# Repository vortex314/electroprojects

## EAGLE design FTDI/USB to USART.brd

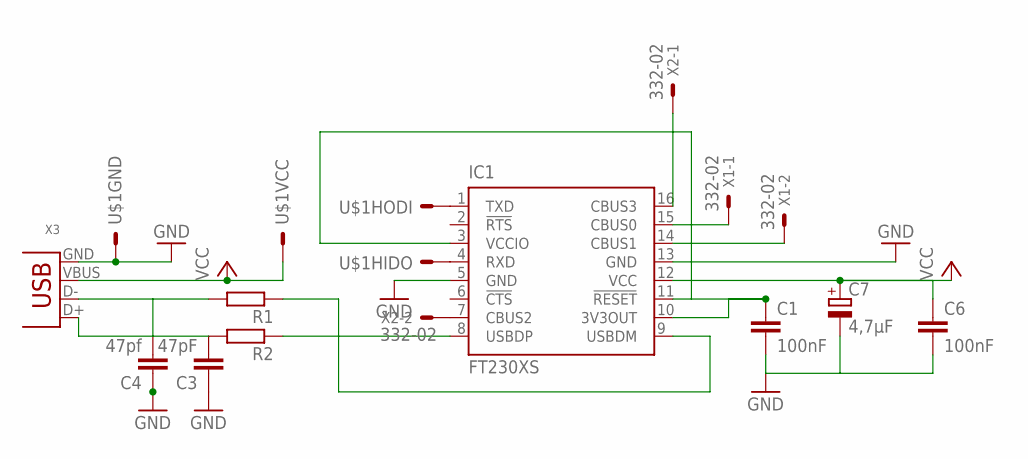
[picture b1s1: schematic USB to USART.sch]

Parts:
C1, C6: 100nF; C025-030X050
C3: 47pF; C025-030X050
C4: 47pf; C025-030X050
C7: 4,7µF; B45181B
IC1: FT230XS; SSOP16
R1, R2: R-EU_0204/7; 0204/7
U$1: UARTUSB; PN61729
X1, X2: 332-02
X3: USB-B-H

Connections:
GND: C1.2, C3.1, C4.1, C6.2, C7.-, IC1.5 (GND), IC1.13 (GND), U$1.4, X3.GND
unnamed: IC1.8 (USBDP), R2.1
unnamed: C3.2, R2.2, X3.D+
unnamed: IC1.9 (USBDM), R1.1
unnamed: C1.1, IC1.3 (VCCIO), IC1.10 (3V3OUT), IC1.11 (!RESET)
unnamed: C4.2, R1.2, X3.D-
unnamed: IC1.1 (TXD), U$1.3
unnamed: IC1.4 (RXD), U$1.2
unnamed: IC1.14 (CBUS1), X1.2
unnamed: IC1.15 (CBUS0), X1.1
unnamed: IC1.16 (CBUS3), X2.1
unnamed: IC1.7 (CBUS2), X2.2
VCC: C6.1, C7.+, IC1.12 (VCC), U$1.1, X3.VBUS

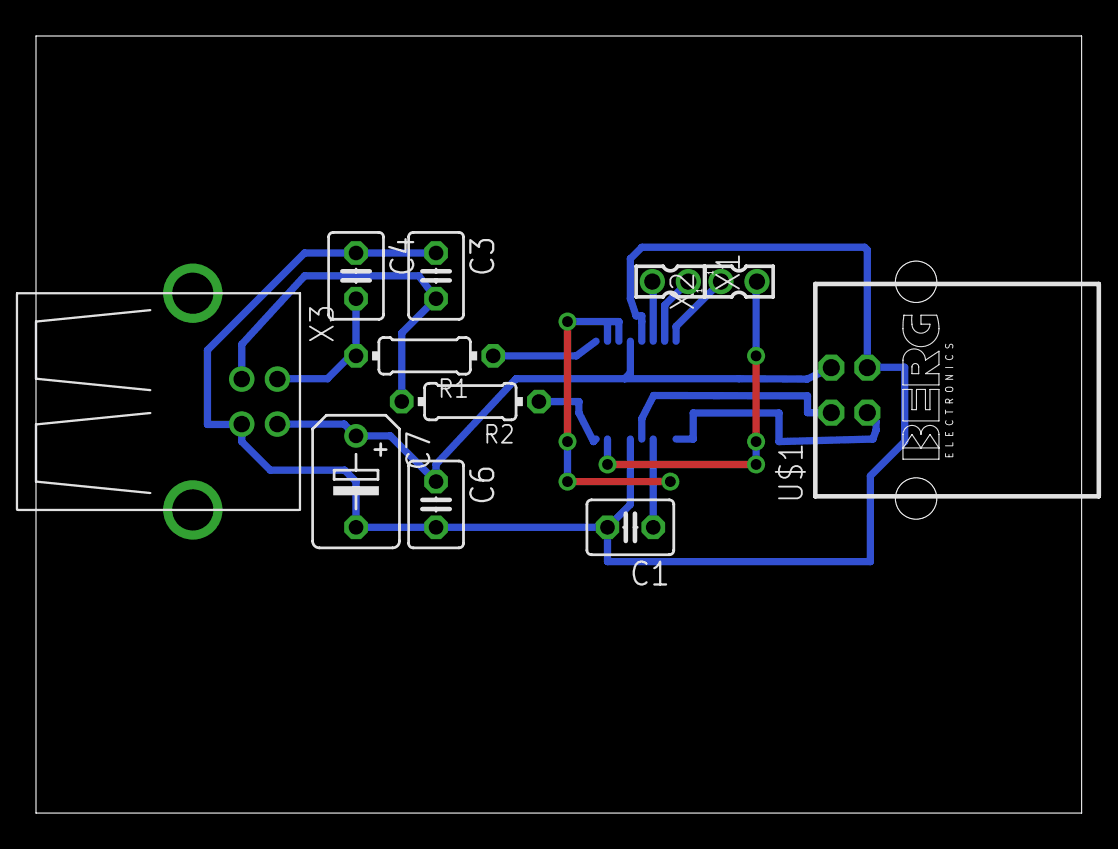
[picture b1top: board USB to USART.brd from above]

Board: 2 copper layers, 58.1 x 43.2 mm, 12 parts (1 on the bottom side), 13 nets.

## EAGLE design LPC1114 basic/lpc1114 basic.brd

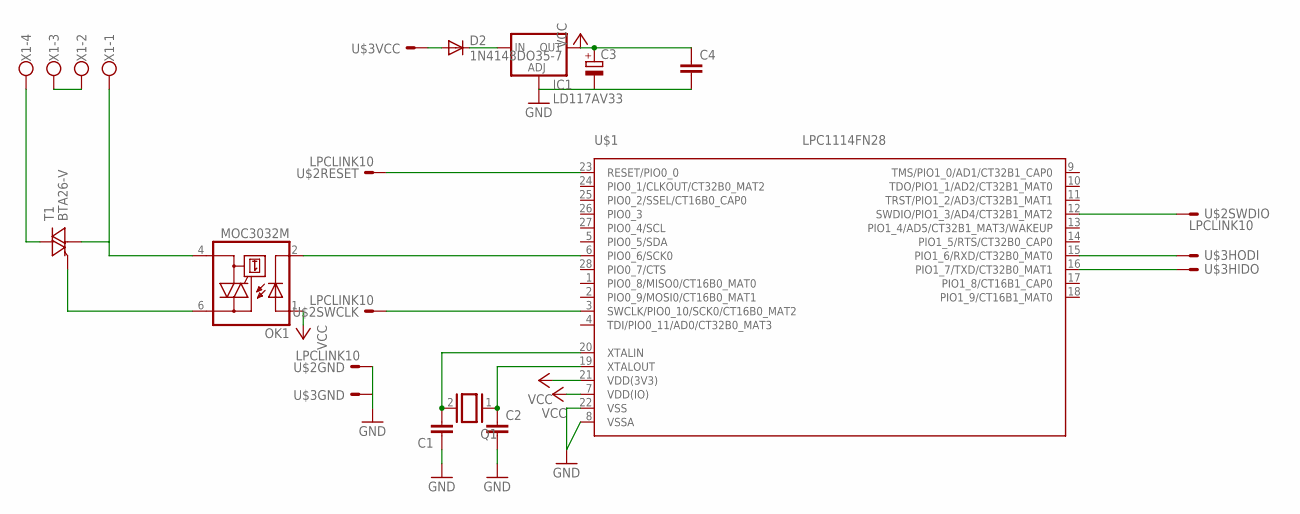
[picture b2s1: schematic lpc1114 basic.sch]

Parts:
C1, C2: C-EU025-024X044; C025-024X044
C3: CPOL-EUTT2D6; TT2D6
C4: C-EU050-024X044; C050-024X044
D2: 1N4148DO35-7; DO35-7
IC1: LD117AV33; TO220L1
OK1: MOC3032M; DIL06
Q1: XTAL/S; QS
T1: BTA26-V; TOP3S-1
U$1: LPC1114FN28; DIP28
U$2: LPCLINK10; ML10
U$3: UARTUSB; PN61729
X1: W237-4

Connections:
GND: C1.1, C2.2, C3.-, C4.2, IC1.1 (ADJ), U$1.8 (VSSA), U$1.22 (VSS), U$2.9, U$3.4
unnamed: C1.2, Q1.2, U$1.20 (XTALIN)
unnamed: C2.1, Q1.1, U$1.19 (XTALOUT)
unnamed: U$1.15 (PIO1_6/RXD/CT32B0_MAT0), U$3.3
unnamed: U$1.16 (PIO1_7/TXD/CT32B0_MAT1), U$3.2
unnamed: U$1.3 (SWCLK/PIO0_10/SCK0/CT16B0_MAT2), U$2.4
unnamed: U$1.12 (SWDIO/PIO1_3/AD4/CT32B1_MAT2), U$2.2
unnamed: U$1.23 (RESET/PIO0_0), U$2.10
unnamed: D2.A, U$3.1
unnamed: OK1.6 (A2), T1.G
unnamed: D2.C, IC1.3 (IN)
unnamed: T1.A2, X1.4
unnamed: OK1.2 (C), U$1.6 (PIO0_6/SCK0)
unnamed: OK1.4 (A1), T1.A1, X1.1
unnamed: X1.2, X1.3
VCC: C3.+, C4.1, IC1.2 (OUT), OK1.1 (A), U$1.7 (VDD(IO)), U$1.21 (VDD(3V3))

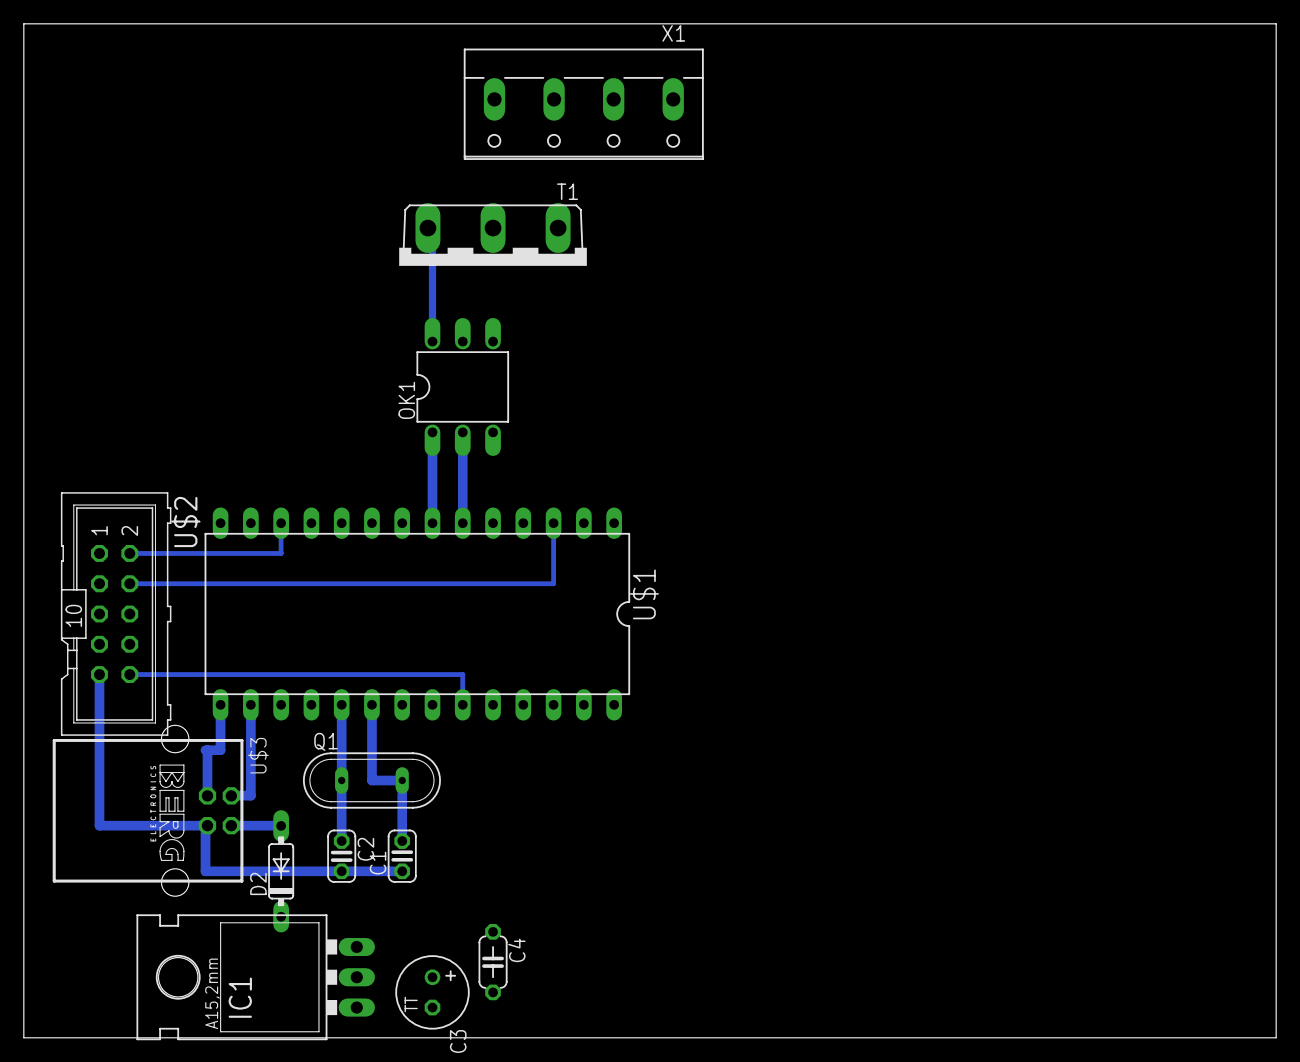
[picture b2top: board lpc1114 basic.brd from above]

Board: 2 copper layers, 105.1 x 85.1 mm, 13 parts (0 on the bottom side), 16 nets.

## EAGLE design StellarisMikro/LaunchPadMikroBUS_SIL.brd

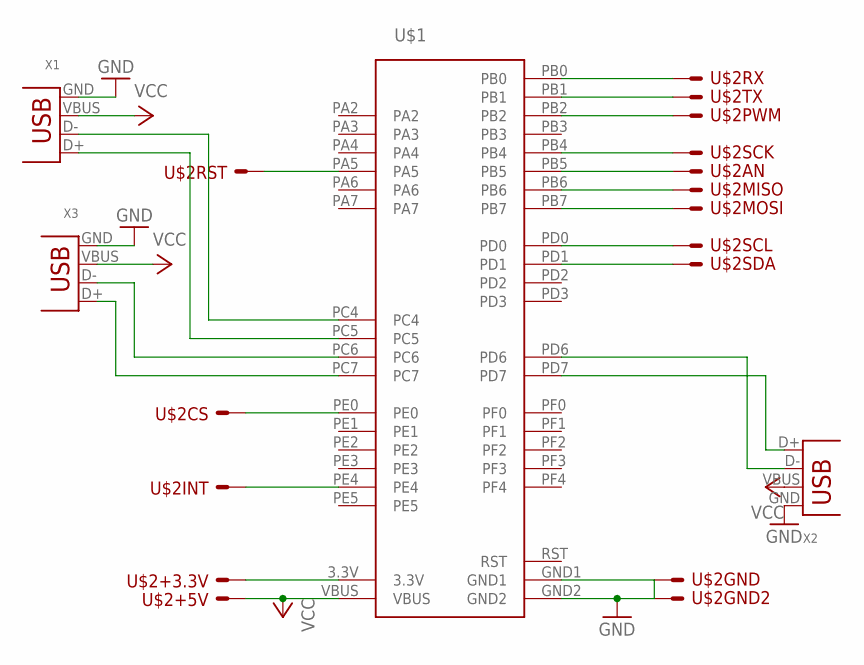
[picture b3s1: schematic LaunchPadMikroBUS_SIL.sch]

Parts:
U$1: STELLARIS-LAUNCHPADSTELLARIS-LAUNCHPAD-XL; LAUNCHPAD-XL
U$2: MIKROBUSSIL; MIKROBUS_SIL
X1, X2, X3: USB-A-H

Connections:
GND: U$1.GND1, U$1.GND2, U$2.GND, U$2.GND2, X1.GND, X2.GND, X3.GND
unnamed: U$1.PB2, U$2.PWM
unnamed: U$1.PE4, U$2.INT
unnamed: U$1.PB0, U$2.RX
unnamed: U$1.PB1, U$2.TX
unnamed: U$1.PD0, U$2.SCL
unnamed: U$1.PD1, U$2.SDA
unnamed: U$1.PC7, X3.D+
unnamed: U$1.PC6, X3.D-
unnamed: U$1.PC5, X1.D+
unnamed: U$1.3.3V, U$2.+3.3V
unnamed: U$1.PB5, U$2.AN
unnamed: U$1.PA5, U$2.RST
unnamed: U$1.PE0, U$2.CS
unnamed: U$1.PB4, U$2.SCK
unnamed: U$1.PB7, U$2.MOSI
unnamed: U$1.PB6, U$2.MISO
unnamed: U$1.PC4, X1.D-
unnamed: U$1.PD7, X2.D+
unnamed: U$1.PD6, X2.D-
RST: U$1.RST
VCC: U$1.VBUS, U$2.+5V, X1.VBUS, X2.VBUS, X3.VBUS

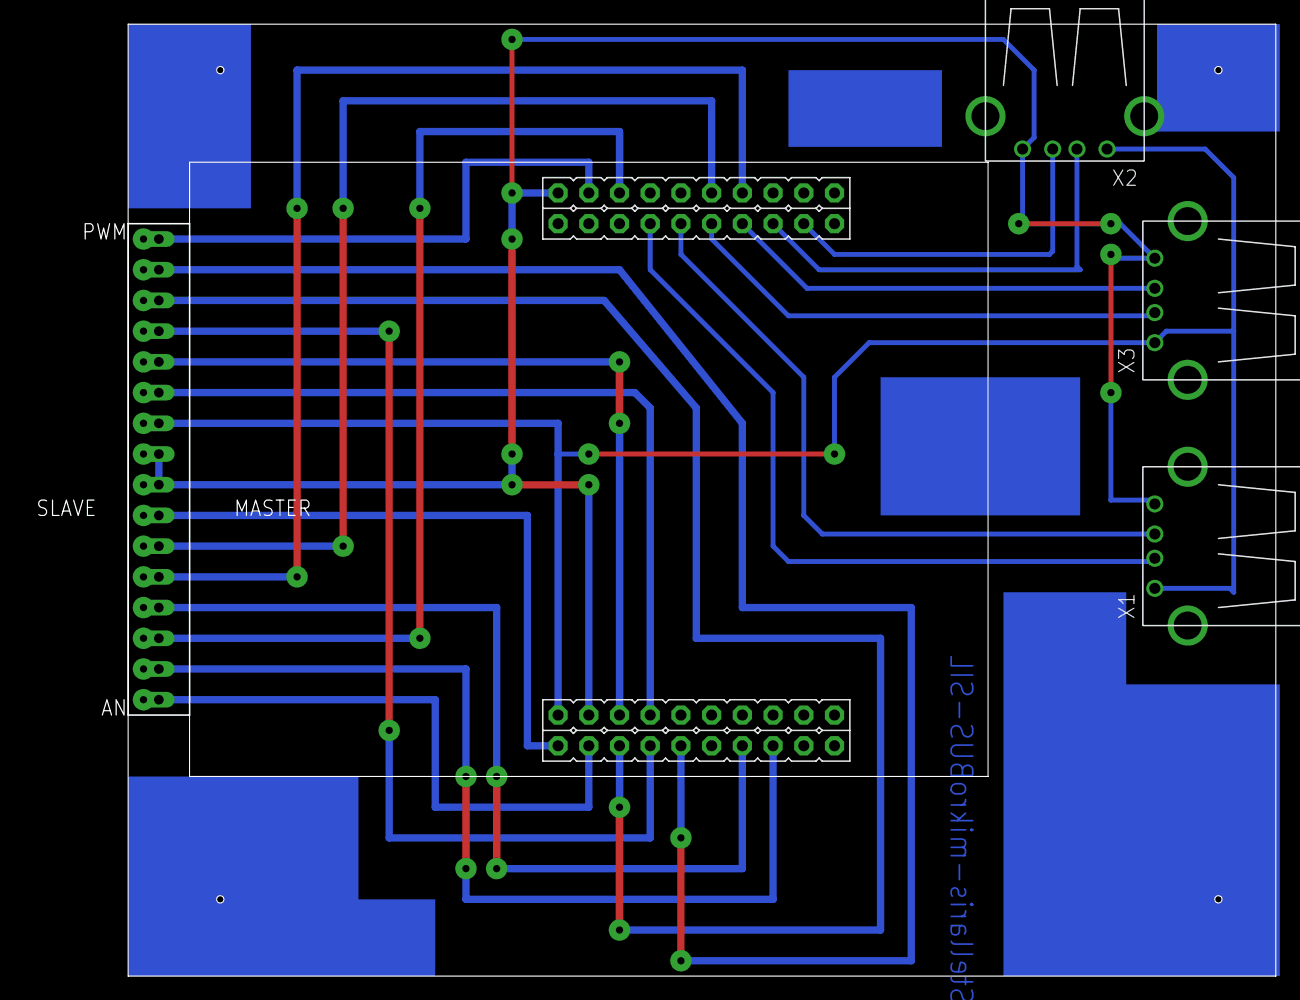
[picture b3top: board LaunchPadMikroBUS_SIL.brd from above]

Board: 2 copper layers, 94.9 x 78.7 mm, 5 parts (0 on the bottom side), 21 nets.

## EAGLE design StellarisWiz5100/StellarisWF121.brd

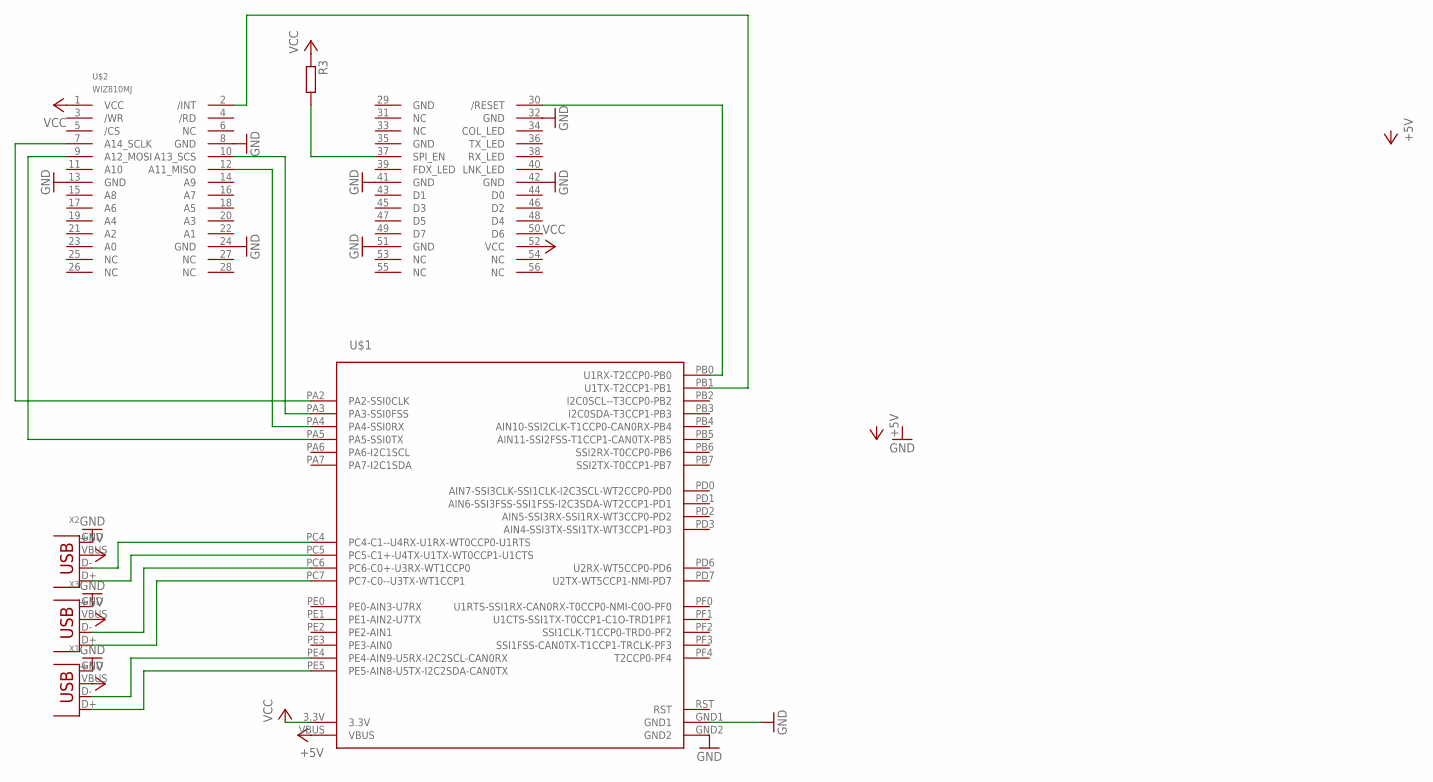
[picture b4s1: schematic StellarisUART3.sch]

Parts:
R3: R-EU_0207/7; 0207/7
U$1: STELLARIS-LAUNCHPADSTELLARIS-LAUNCHPAD-XL; LAUNCHPAD-XL
U$2: WIZ810MJ
X1, X2, X3: USB-A-H

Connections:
3.3V: U$1.3.3V
+5V: U$1.VBUS, X1.VBUS, X2.VBUS, X3.VBUS
GND: U$1.GND1, U$1.GND2, U$2.8 (GND), U$2.13 (GND), U$2.24 (GND), U$2.32 (GND), U$2.41 (GND), U$2.42 (GND), U$2.51 (GND), X1.GND, X2.GND, X3.GND
unnamed: U$1.PB0 (U1RX-T2CCP0-PB0), U$2.30 (/RESET)
unnamed: U$1.PE5 (PE5-AIN8-U5TX-I2C2SDA-CAN0TX), X1.D+
unnamed: U$1.PA2 (PA2-SSI0CLK), U$2.7 (A14_SCLK)
unnamed: U$1.PE4 (PE4-AIN9-U5RX-I2C2SCL-CAN0RX), X1.D-
unnamed: U$1.PB1 (U1TX-T2CCP1-PB1), U$2.2 (/INT)
unnamed: U$1.PA5 (PA5-SSI0TX), U$2.9 (A12_MOSI)
unnamed: U$1.PA4 (PA4-SSI0RX), U$2.12 (A11_MISO)
unnamed: U$1.PA3 (PA3-SSI0FSS), U$2.10 (A13_SCS)
unnamed: R3.2, U$2.37 (SPI_EN)
unnamed: U$1.PC4 (PC4-C1--U4RX-U1RX-WT0CCP0-U1RTS), X2.D-
unnamed: U$1.PC5 (PC5-C1+-U4TX-U1TX-WT0CCP1-U1CTS), X2.D+
unnamed: U$1.PC6 (PC6-C0+-U3RX-WT1CCP0), X3.D-
unnamed: U$1.PC7 (PC7-C0--U3TX-WT1CCP1), X3.D+
RST: U$1.RST
VCC: R3.1, U$2.1 (VCC), U$2.52 (VCC)

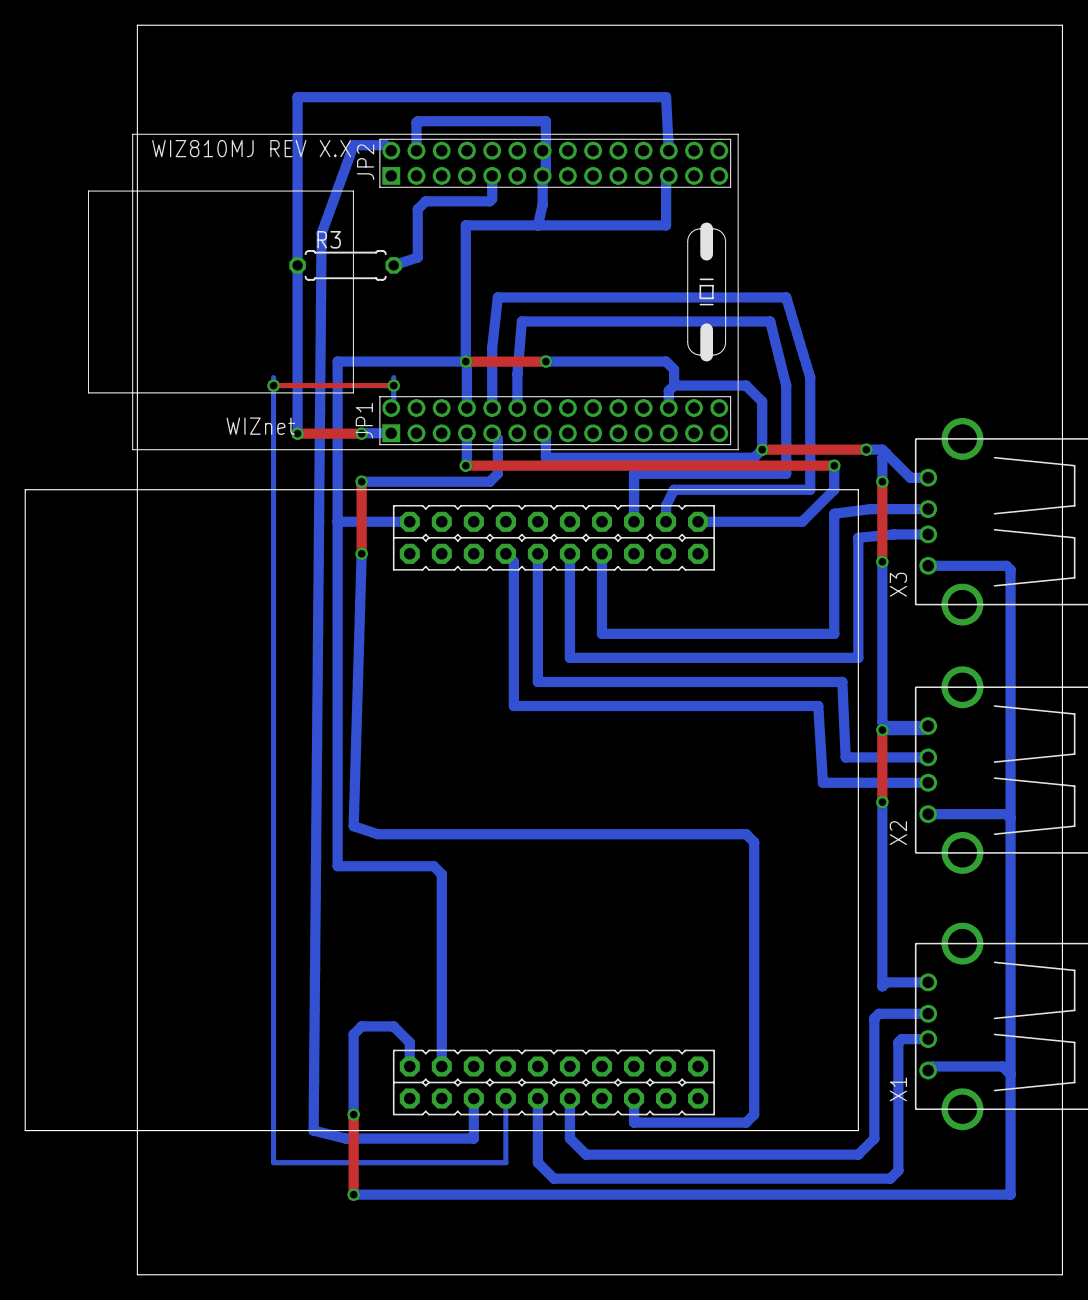
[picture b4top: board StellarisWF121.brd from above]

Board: 2 copper layers, 82.2 x 99.0 mm, 6 parts (0 on the bottom side), 16 nets.

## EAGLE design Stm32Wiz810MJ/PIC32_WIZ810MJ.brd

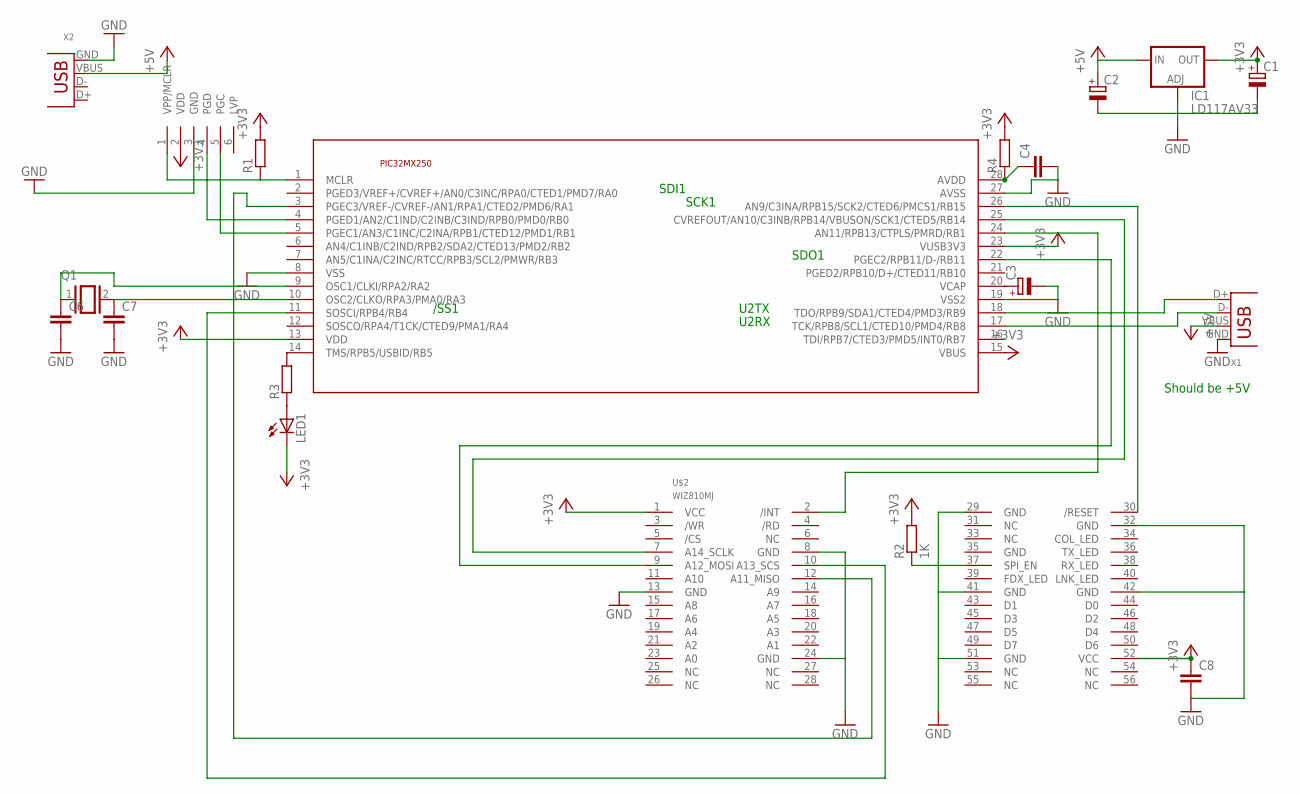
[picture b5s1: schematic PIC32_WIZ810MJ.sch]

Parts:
C1, C2: CPOL-EUE3.5-10; E3,5-10
C3: CPOL-EUE2.5-6; E2,5-6
C4, C8: C-EU050-055X075; C050-055X075
C6, C7: C-EU025-025X050; C025-025X050
IC1: LD117AV33; TO220L1
LED1: LED_ELD260; LED_LD260
Q1: XTAL/S; QS
R1, R3, R4: R-EU_0204/5; 0204/5
R2: 1K; 0204/5
U$1: PIC32MX2XXDIP28_SLIM; DIP254P762X508-28
U$2: WIZ810MJ
U$3: ICSP-6_6P; 1X06-CLEANBIG
X1: USB-A-H
X2: USB-B-H

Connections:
+3V3: C1.+, C8.1, IC1.2 (OUT), LED1.K (C), R1.2, R2.2, R4.2, U$1.13 (VDD), U$1.15 (VBUS), U$1.23 (VUSB3V3), U$2.1 (VCC), U$2.52 (VCC), U$3.2 (VDD)
+5V: C2.+, IC1.3 (IN), X1.VBUS, X2.VBUS
GND: C1.-, C2.-, C3.-, C4.2, C6.2, C7.2, C8.2, IC1.1 (ADJ), U$1.8 (VSS), U$1.19 (VSS2), U$1.27 (AVSS), U$2.8 (GND), U$2.13 (GND), U$2.24 (GND), U$2.29 (GND), U$2.32 (GND), U$2.41 (GND), U$2.42 (GND), U$2.51 (GND), U$3.3 (GND), X1.GND, X2.GND
unnamed: U$1.22 (PGEC2/RPB11/D-/RB11), U$2.9 (A12_MOSI)
unnamed: U$1.3 (PGEC3/VREF-/CVREF-/AN1/RPA1/CTED2/PMD6/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), U$2.12 (A11_MISO)
unnamed: U$1.25 (CVREFOUT/AN10/C3INB/RPB14/VBUSON/SCK1/C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), U$2.7 (A14_SCLK)
unnamed: R1.1, U$1.1 (MCLR), U$3.1 (VPP/MCLR)
unnamed: U$1.11 (SOSCI/RPB4/RB4), U$2.10 (A13_SCS)
unnamed: U$1.4 (PGED1/AN2/C1IND/C2INB/C3IND/RPB0/PMD0/R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), U$3.4 (PGD)
unnamed: U$1.26 (AN9/C3INA/RPB15/SCK2/CTED6/PMCS1/RB15), U$2.30 (/RESET)
unnamed: U$1.5 (PGEC1/AN3/C1INC/C2INA/RPB1/CTED12/PMD1/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), U$3.5 (PGC)
unnamed: U$1.18 (TDO/RPB9/SDA1/CTED4/PMD3/RB9), X1.D+
unnamed: U$1.17 (TCK/RPB8/SCL1/CTED10/PMD4/RB8), X1.D-
unnamed: R2.1, U$2.37 (SPI_EN)
unnamed: C4.1, R4.1, U$1.28 (AVDD)
unnamed: U$1.24 (AN11/RPB13/CTPLS/PMRD/RB1), U$2.2 (/INT)
unnamed: C6.1, Q1.1, U$1.9 (OSC1/CLKI/RPA2/RA2)
unnamed: C7.1, Q1.2, U$1.10 (OSC2/CLKO/RPA3/PMA0/RA3)
unnamed: R3.2, U$1.14 (TMS/RPB5/USBID/RB5)
unnamed: LED1.A, R3.1
unnamed: C3.+, U$1.20 (VCAP)

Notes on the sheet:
U2TX
U2RX
SDI1
SDO1
SCK1
/SS1
Should be +5V

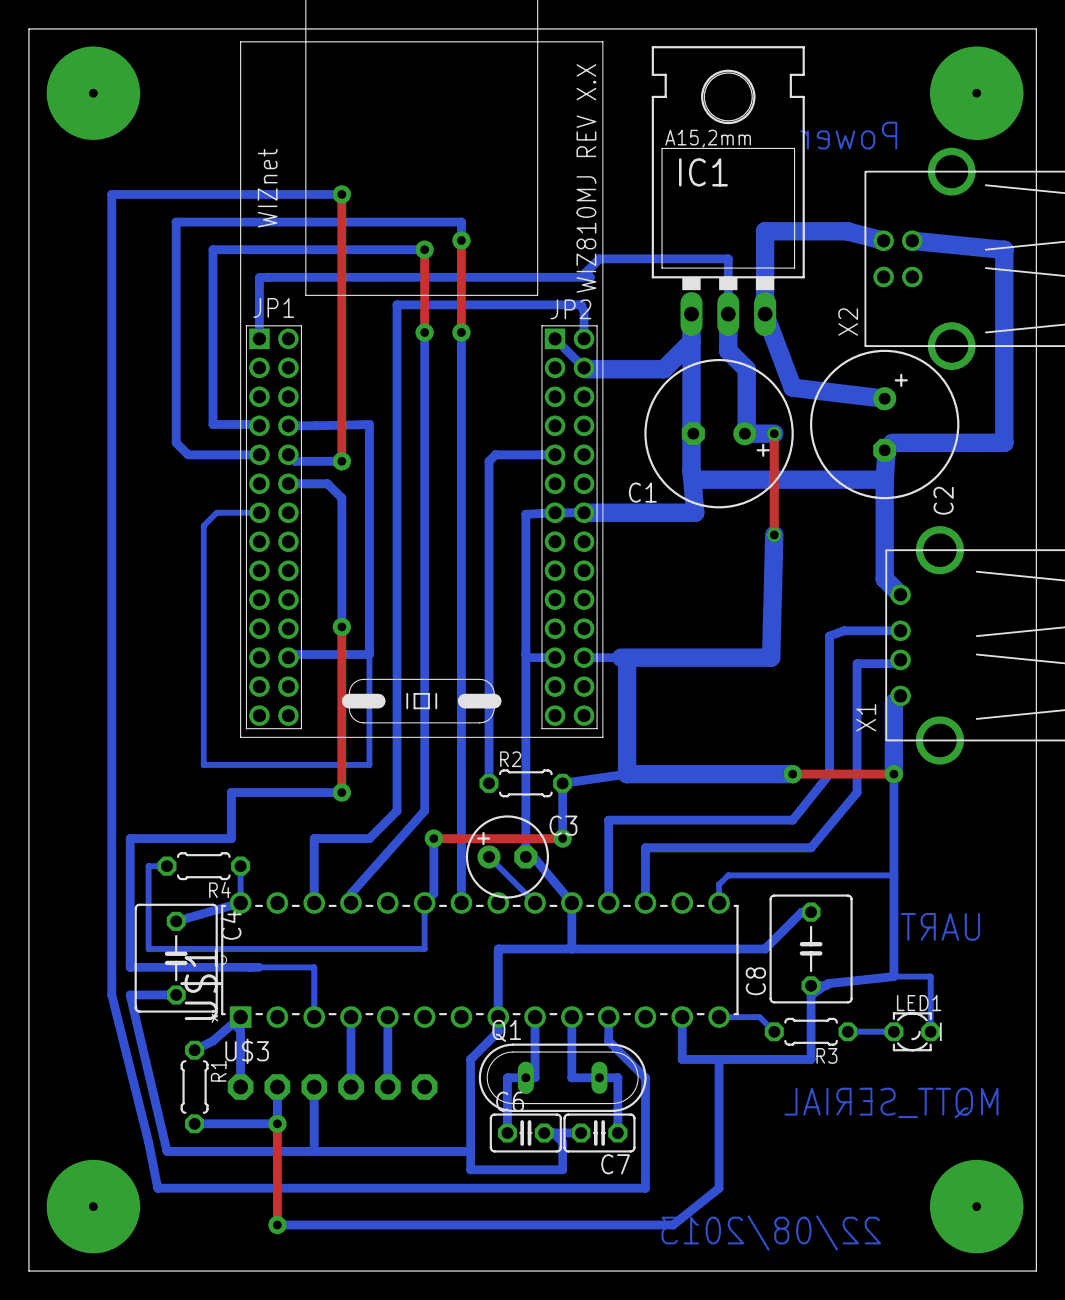
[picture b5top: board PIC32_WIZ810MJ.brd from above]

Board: 2 copper layers, 69.5 x 85.7 mm, 19 parts (0 on the bottom side), 21 nets.
